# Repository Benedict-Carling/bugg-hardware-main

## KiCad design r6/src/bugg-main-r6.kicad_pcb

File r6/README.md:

# Bugg r6 main board (unofficial, unbuilt)

An experimental revision of the Bugg r5 main board by Benedict Carling (Alauda). **It is not an official Bugg release, and no r6 board has been built or measured.**

It is derived from `r5/src` at commit `e71fd5740865aec2923b8e5c67f93d5d7822d4b3` of [bugg-resources/bugg-hardware-main](https://github.com/bugg-resources/bugg-hardware-main), and is licensed CC BY-NC-SA 4.0 like the original, with credit to Bugg's original hardware authors.

## How it was made

The schematic changes, placement and routing were produced with AI coding agents driving KiCad through scripts, and reviewed by me. The review documents in `review/` are AI-assisted review passes. The design has not been reviewed by an independent electronics engineer.

## What changed

- **Plug-in microphone bias filter.** R104 goes from 0 Ω to 100 Ω with the existing 10 µF C83: calculated 34 dB supply-ripple rejection at 8 kHz, or 26 dB if C83 derates to 4 µF. Q25 (the P3V3 mic-power switch) now takes its supply from before R104, so that output keeps its full voltage.
- **ADC input filter.** C75/C76 go from 180 pF to 4.7 nF C0G: calculated 18 dB more rejection at 1.38 MHz and 0.06 dB loss at 20 kHz. This is an experimental 44.1/48 kHz population; 180 pF remains the alternative.
- **Real-time clock.** The DS3231M becomes an RV-3032-C7: ±2.5 ppm instead of ±5 ppm initial specification over −40 to +85 °C, excluding aging.
- **Wake buffer.** U14 becomes an SN74LVC1G37 in the same footprint, with a Schmitt input suited to the slow RC wake edge. R29/R30/C36 become 100 kΩ / 47 kΩ / 1 µF.
- **3.3 V always-on rail.** A TPS7A02 regulator powers the clock, the wake logic and the voltage monitor, which r5 ran from the approximately 5.4 V system rail against 5.5 V part limits.
- **Supply voltage monitoring.** An ADS1115 measures the input, system, modem and USB rails. It measures voltage only, not current or battery charge.
- **Modem shutdown confirmation.** VGPIO and SAFE_PWR_REMOVE are level-shifted and latched, then read over I²C. This addresses r5 erratum 5.

The full part list is in [review/BOM-CHANGES.md](review/BOM-CHANGES.md): 8 changed, 33 added.

## What did not change

- **Board:** the outline, the six-layer stack and the 1.6 mm thickness.
- **Fixed interfaces:** all 37 keep their position, rotation, side and pad geometry. That covers the CM4, the modem, the USB, J10 and FH12 connectors, both U.FL connectors, the SIM, microSD and coin-cell holders, the mounting holes, bosses, ground contacts, J1–J9 and the fiducials.
- **Copper and test points:** the USB and microphone-input traces are identical to r5, and all 59 r5 test points remain.

## Caveats

- **Nothing is measured.** All figures are calculations or datasheet specifications. There is no claim of lower recorded self-noise, longer battery life or better reliability.
- **KiCad 10 is required.** The files were saved in KiCad 10 format, so the diff against r5 includes format changes.
- **Some sheets were regenerated by script.** The RTC sheet and the two new sheets were written by script rather than edited by hand, so the schematic diffs are larger than the actual changes.
- **Not a drop-in r5 image.** The new RTC and monitoring need Bugg OS integration, and `firmware/` contains support code with 22 unit tests against simulated hardware.
- **Still to validate on a prototype:** ADC settling and distortion, microphone noise, wake timing, modem shutdown timing, power sequencing and enclosure fit.

## Reproducing the checks

Run these from `r6/`:

| Command | What it does |
|---|---|
| `<KiCad 10 python> design/verify_board.py` | Compares the board against `r5/src` and checks schematic/PCB pad nets |
| `python3 design/calculations.py` | Recomputes the filter and clock figures from the netlist |
| `python3 design/bom.py` | Regenerates the BOM delta |
| `cd firmware && python3 -m unittest discover -p 'test_*.py'` | Runs the firmware tests |

The native KiCad results are recorded in `review/final-drc.json` and `review/erc.json`: 0 DRC errors, 0 unconnected items, 0 schematic-parity issues and 0 ERC errors.

Start with [review/REPORT.md](review/REPORT.md). [review/AUDIO-EXPLAINED.md](review/AUDIO-EXPLAINED.md) explains what the filter figures mean for recordings.

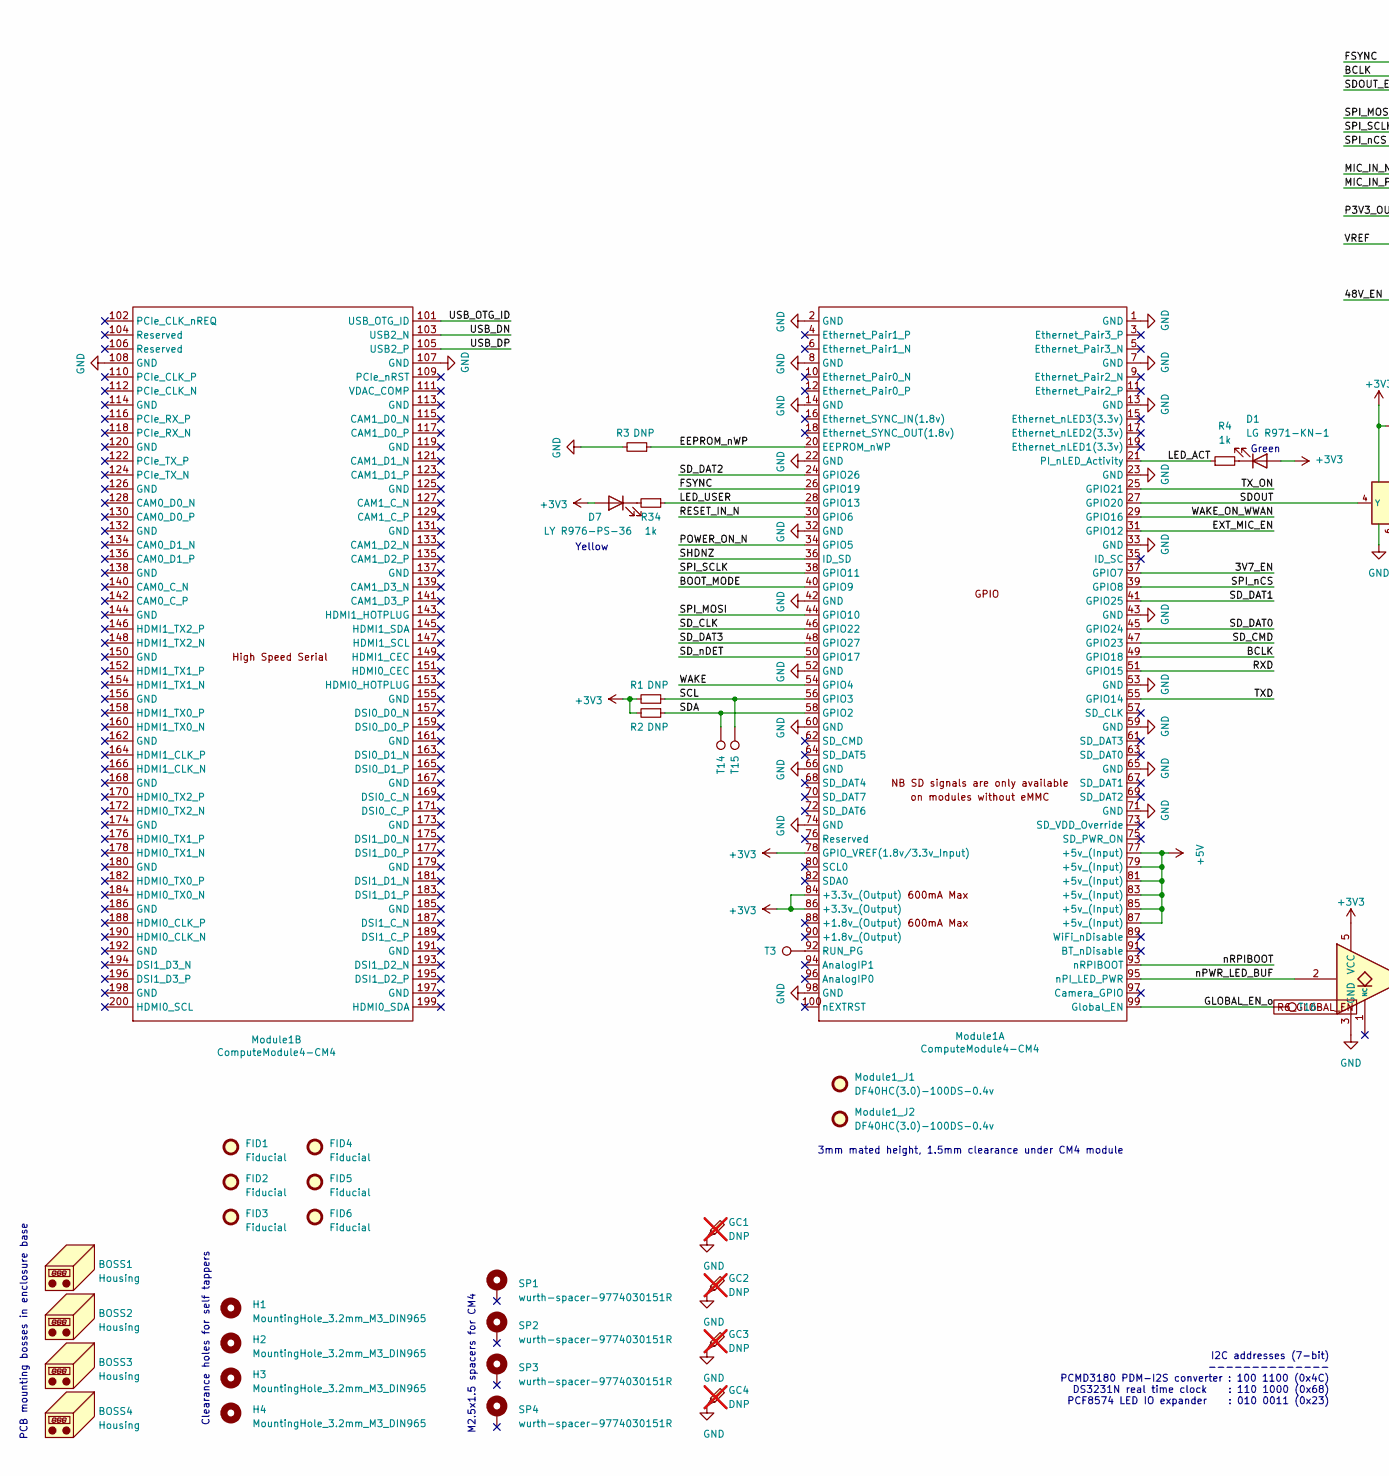
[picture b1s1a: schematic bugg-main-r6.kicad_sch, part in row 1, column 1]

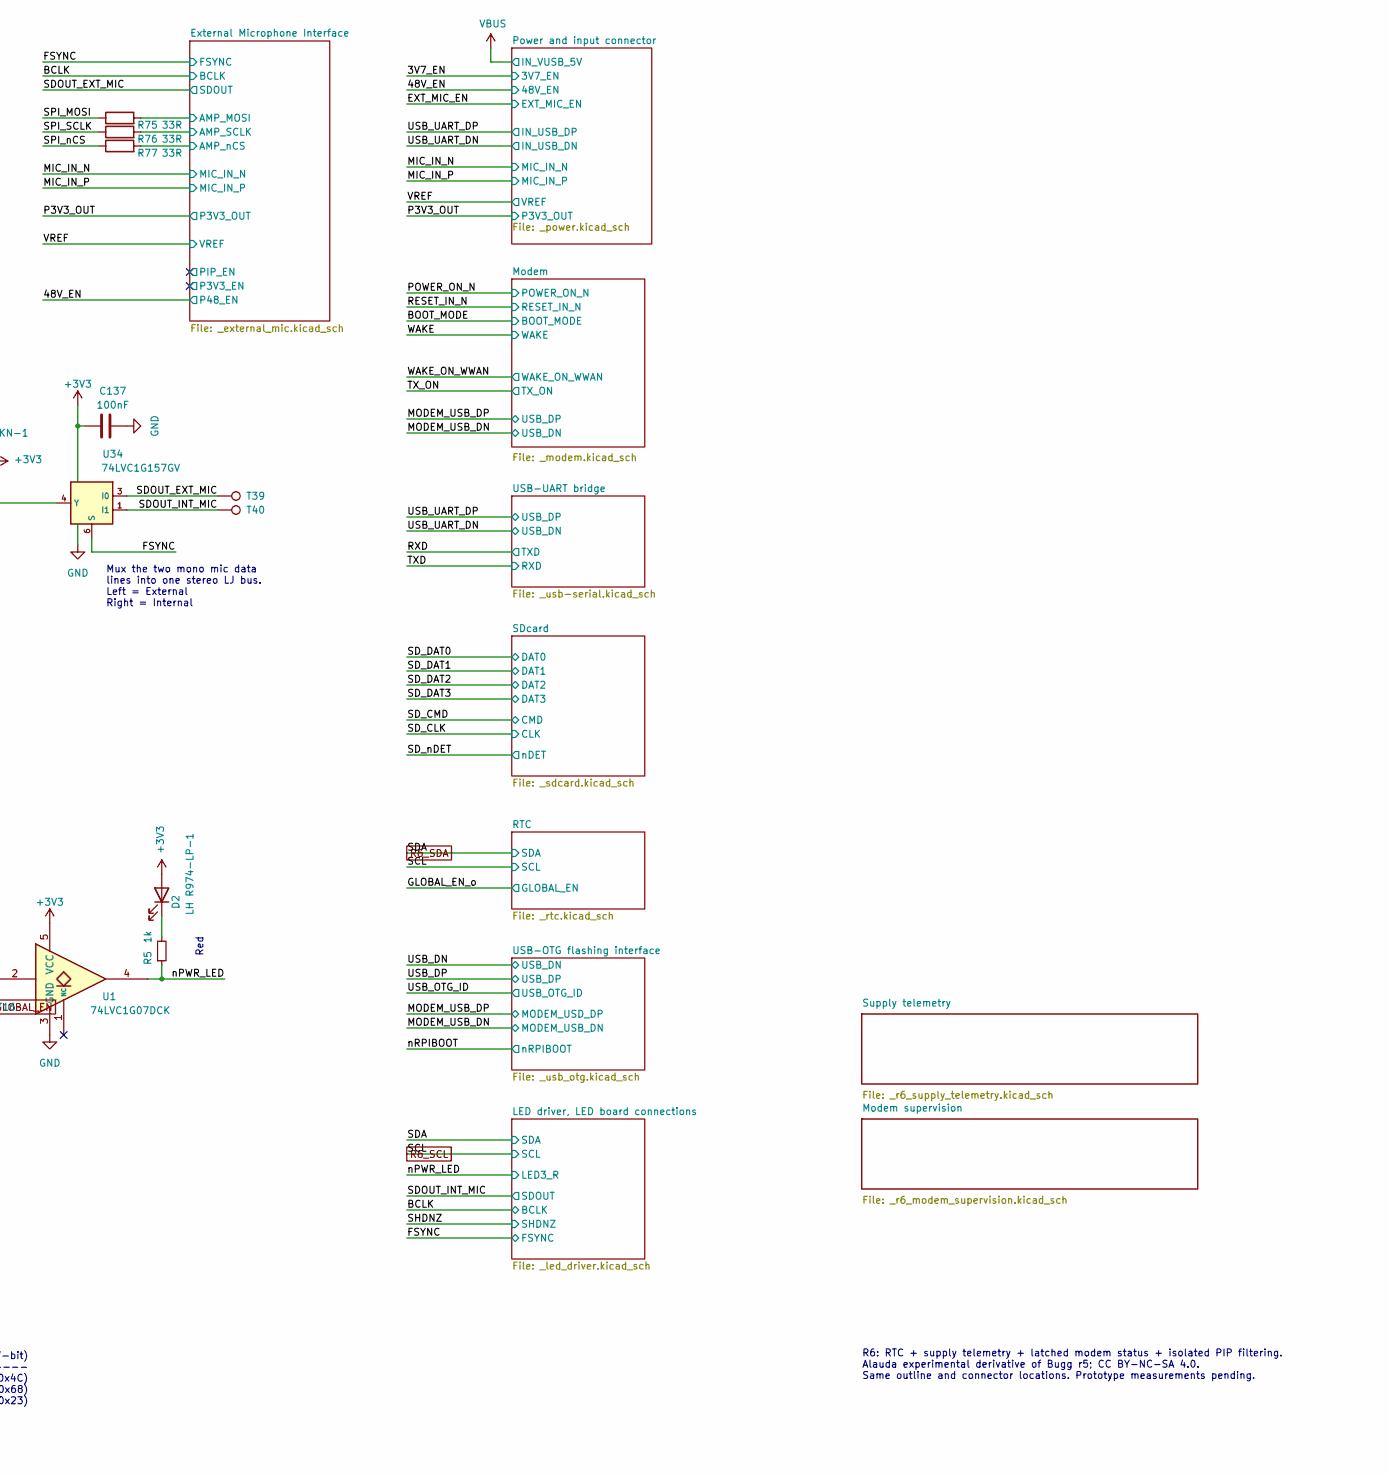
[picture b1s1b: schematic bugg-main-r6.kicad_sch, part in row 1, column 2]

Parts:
BOSS1, BOSS2, BOSS3, BOSS4: Housing; bugg-pcb-boss
C137: 100nF; C_0402_1005Metric; Voltage 50V; MPN GRM155R71H104KE14D; Mouser 81-GRM155R71H104KE4D
D1: LG R971-KN-1; CHIPLED-0805; MPN LGR971-KN-1; Digikey 475-1410-6-ND
D2: LH R974-LP-1; CHIPLED-0805; MPN LHR974-LP-1; Digikey 475-1415-6-ND
D7: LY R976-PS-36; CHIPLED-0805; MPN LYR976-PS-36; Digikey 475-2560-6-ND
FID1, FID2, FID3, FID4, FID5, FID6: Fiducial; Fiducial_1mm_Mask2mm
GC1, GC2, GC3, GC4: DNP; TestPoint_Keystone_5019_Minature; MPN 5019; Mouser 534-5019; not fitted
H1, H2, H3, H4: MountingHole_3.2mm_M3_DIN965
Module1: ComputeModule4-CM4; Raspberry-Pi-4-Compute-Module-no-holes; MPN CM4002016; Farnell 3563481
Module1_J1, Module1_J2: DF40HC(3.0)-100DS-0.4v; MPN DF40HC(3.0)-100DS-0.4v; Digikey H124602DKR-ND
R1, R2, R3: DNP; R_0402_1005Metric
R4, R5, R34: 1k; R_0402_1005Metric
R75, R76, R77: 33R; R_0402_1005Metric
SP1, SP2, SP3, SP4: wurth-spacer-9774030151R; wurth-spacer-WA-SMSI-9774030151R; MPN 9774030151R; Digikey 732-7083-6-ND
T3, T14, T15, T16, T39, T40: TestPoint_Pad_D1.0mm
U1: 74LVC1G07DCK; SOT-353_SC-70-5; MPN SN74LVC1G07DCKT; Digikey 296-26591-6-ND
U34: 74LVC1G157GV; SC-74-6_1.5x2.9mm_P0.95mm; MPN 74LVC1G157GV; Mouser 771-74LVC1G157GVQ100

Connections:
+3V3: C137.2, D1.2 (A), D2.2 (A), D7.2 (A), Module1.78 (GPIO_VREF(1.8v/3.3v_Input)), Module1.84 (+3.3v_(Output)), Module1.86 (+3.3v_(Output)), R1.2, R2.2, U1.5 (VCC), U34.5 (VCC); also elsewhere on the board
+5V: Module1.77 (+5v_(Input)), Module1.79 (+5v_(Input)), Module1.81 (+5v_(Input)), Module1.83 (+5v_(Input)), Module1.85 (+5v_(Input)), Module1.87 (+5v_(Input)); also elsewhere on the board
/3V7_EN: Module1.37 (GPIO7); also elsewhere on the board
/BCLK: Module1.49 (GPIO18); also elsewhere on the board
/BOOT_MODE: Module1.40 (GPIO9); also elsewhere on the board
/EEPROM_nWP: Module1.20 (EEPROM_nWP), R3.1
/EXT_MIC_EN: Module1.31 (GPIO12); also elsewhere on the board
/External Microphone Interface/AMP_MOSI: R75.2; also elsewhere on the board
/External Microphone Interface/AMP_SCLK: R76.2; also elsewhere on the board
/External Microphone Interface/AMP_nCS: R77.2; also elsewhere on the board
/FSYNC: Module1.26 (GPIO19), U34.6 (S); also elsewhere on the board
/LED_ACT: Module1.21 (PI_nLED_Activity), R4.1
/LED_USER: Module1.28 (GPIO13), R34.1
/POWER_ON_N: Module1.34 (GPIO5); also elsewhere on the board
/RESET_IN_N: Module1.30 (GPIO6); also elsewhere on the board
/RXD: Module1.51 (GPIO15); also elsewhere on the board
/SDOUT: Module1.27 (GPIO20), U34.4 (Y)
/SDOUT_EXT_MIC: T39.1, U34.3 (I0); also elsewhere on the board
/SDOUT_INT_MIC: T40.1, U34.1 (I1); also elsewhere on the board
/SD_CLK: Module1.46 (GPIO22); also elsewhere on the board
/SD_CMD: Module1.47 (GPIO23); also elsewhere on the board
/SD_DAT0: Module1.45 (GPIO24); also elsewhere on the board
/SD_DAT1: Module1.41 (GPIO25); also elsewhere on the board
/SD_DAT2: Module1.24 (GPIO26); also elsewhere on the board
/SD_DAT3: Module1.48 (GPIO27); also elsewhere on the board
/SD_nDET: Module1.50 (GPIO17); also elsewhere on the board
/SHDNZ: Module1.36 (ID_SD); also elsewhere on the board
/SPI_MOSI: Module1.44 (GPIO10), R75.1
/SPI_SCLK: Module1.38 (GPIO11), R76.1
/SPI_nCS: Module1.39 (GPIO8), R77.1
/TXD: Module1.55 (GPIO14); also elsewhere on the board
/TX_ON: Module1.25 (GPIO21); also elsewhere on the board
/USB_DN: Module1.103 (USB2_N); also elsewhere on the board
/USB_DP: Module1.105 (USB2_P); also elsewhere on the board
/USB_OTG_ID: Module1.101 (USB_OTG_ID); also elsewhere on the board
/WAKE: Module1.54 (GPIO4); also elsewhere on the board
/WAKE_ON_WWAN: Module1.29 (GPIO16); also elsewhere on the board
/nPWR_LED: R5.1, U1.4; also elsewhere on the board
/nPWR_LED_BUF: Module1.95 (nPI_LED_PWR), U1.2
/nRPIBOOT: Module1.93 (nRPIBOOT); also elsewhere on the board
GND: C137.1, GC1.1, GC2.1, GC3.1, GC4.1, Module1.1 (GND), Module1.2 (GND), Module1.7 (GND), Module1.8 (GND), Module1.13 (GND), Module1.14 (GND), Module1.22 (GND), Module1.23 (GND), Module1.32 (GND), Module1.33 (GND), Module1.42 (GND), Module1.43 (GND), Module1.52 (GND), Module1.53 (GND), Module1.59 (GND), Module1.60 (GND), Module1.65 (GND), Module1.66 (GND), Module1.71 (GND), Module1.74 (GND), Module1.98 (GND), Module1.107 (GND), Module1.108 (GND), R3.2, U1.3 (GND), U34.2 (GND); also elsewhere on the board
unnamed: D1.1 (K), R4.2
unnamed: D2.1 (K), R5.2
unnamed: D7.1 (K), R34.2
unnamed: Module1.92 (RUN_PG), T3.1
R6_GLOBAL_EN: Module1.99 (Global_EN), T16.1; also elsewhere on the board
R6_SCL: Module1.56 (GPIO3), R1.1, T15.1; also elsewhere on the board
R6_SDA: Module1.58 (GPIO2), R2.1, T14.1; also elsewhere on the board

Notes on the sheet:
Yellow
Red
Mux the two mono mic data lines into one stereo LJ bus. Left = External Right = Internal
Green
3mm mated height, 1.5mm clearance under CM4 module
PCB mounting bosses in enclosure base
Clearance holes for self tappers
I2C addresses (7-bit) -------------- PCMD3180 PDM-I2S converter : 100 1100 (0x4C) DS3231N real time clock : 110 1000 (0x68) PCF8574 LED IO expander : 010 0011 (0x23)
M2.5x1.5 spacers for CM4
R6: RTC + supply telemetry + latched modem status + isolated PIP filtering. Alauda experimental derivative of Bugg r5; CC BY-NC-SA 4.0. Same outline and connector locations. Prototype measurements pending.

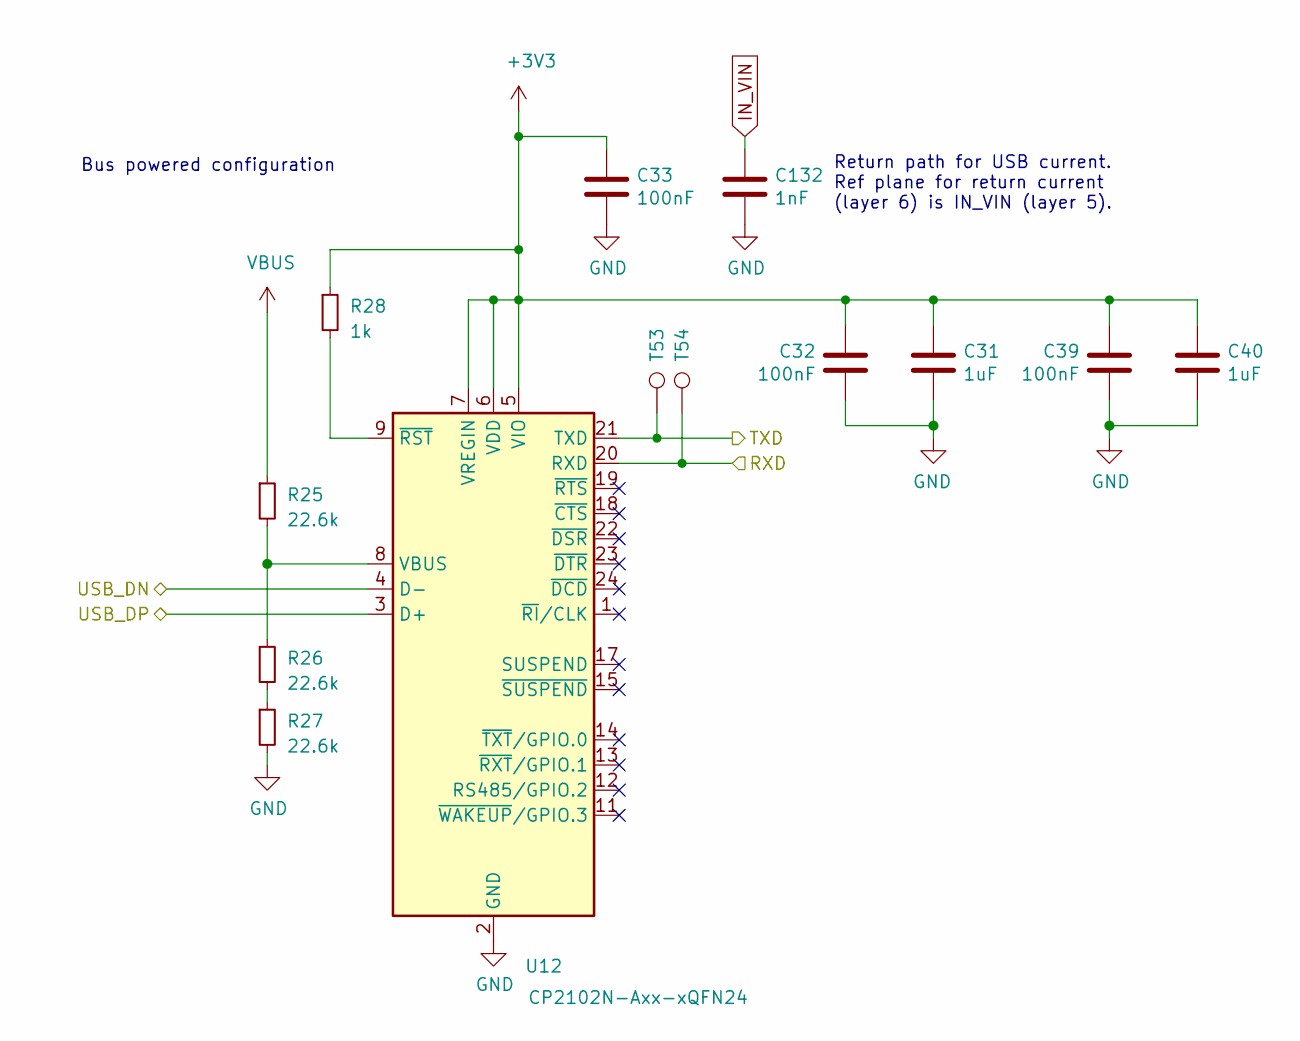
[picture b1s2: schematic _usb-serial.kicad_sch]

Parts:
C31, C40: 1uF; C_0402_1005Metric; Voltage 6.3V; MPN GRM155C81C105KE15D; Mouser 81-GRM155C81C105KE5D
C32, C33, C39: 100nF; C_0402_1005Metric; Voltage 50V; MPN GRM155R71H104KE14D; Mouser 81-GRM155R71H104KE4D
C132: 1nF; C_0402_1005Metric
R25, R26, R27: 22.6k; R_0402_1005Metric
R28: 1k; R_0402_1005Metric
T53, T54: TestPoint_Pad_D1.0mm
U12: CP2102N-Axx-xQFN24; QFN-24-1EP_4x4mm_P0.5mm_EP2.6x2.6mm; MPN CP2102N-A02-GQFN24R; Digikey 336-5888-6-ND

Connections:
+3V3: C31.1, C32.1, C33.1, C39.1, C40.1, R28.1, U12.5 (VIO), U12.6 (VDD), U12.7 (VREGIN); also elsewhere on the board
/RXD: T53.1, U12.21 (TXD); also elsewhere on the board
/TXD: T54.1, U12.20 (RXD); also elsewhere on the board
/USB_UART_DN: U12.4 (D-); also elsewhere on the board
/USB_UART_DP: U12.3 (D+); also elsewhere on the board
GND: C31.2, C32.2, C33.2, C39.2, C40.2, C132.2, R27.2, U12.2 (GND), U12.25 (GND); also elsewhere on the board
IN_VIN: C132.1; also elsewhere on the board
unnamed: R26.2, R27.1
unnamed: R25.2, R26.1, U12.8 (VBUS)
unnamed: R28.2, U12.9 (~RST)
VBUS: R25.1; also elsewhere on the board

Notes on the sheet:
Return path for USB current. Ref plane for return current (layer 6) is IN_VIN (layer 5).
Bus powered configuration

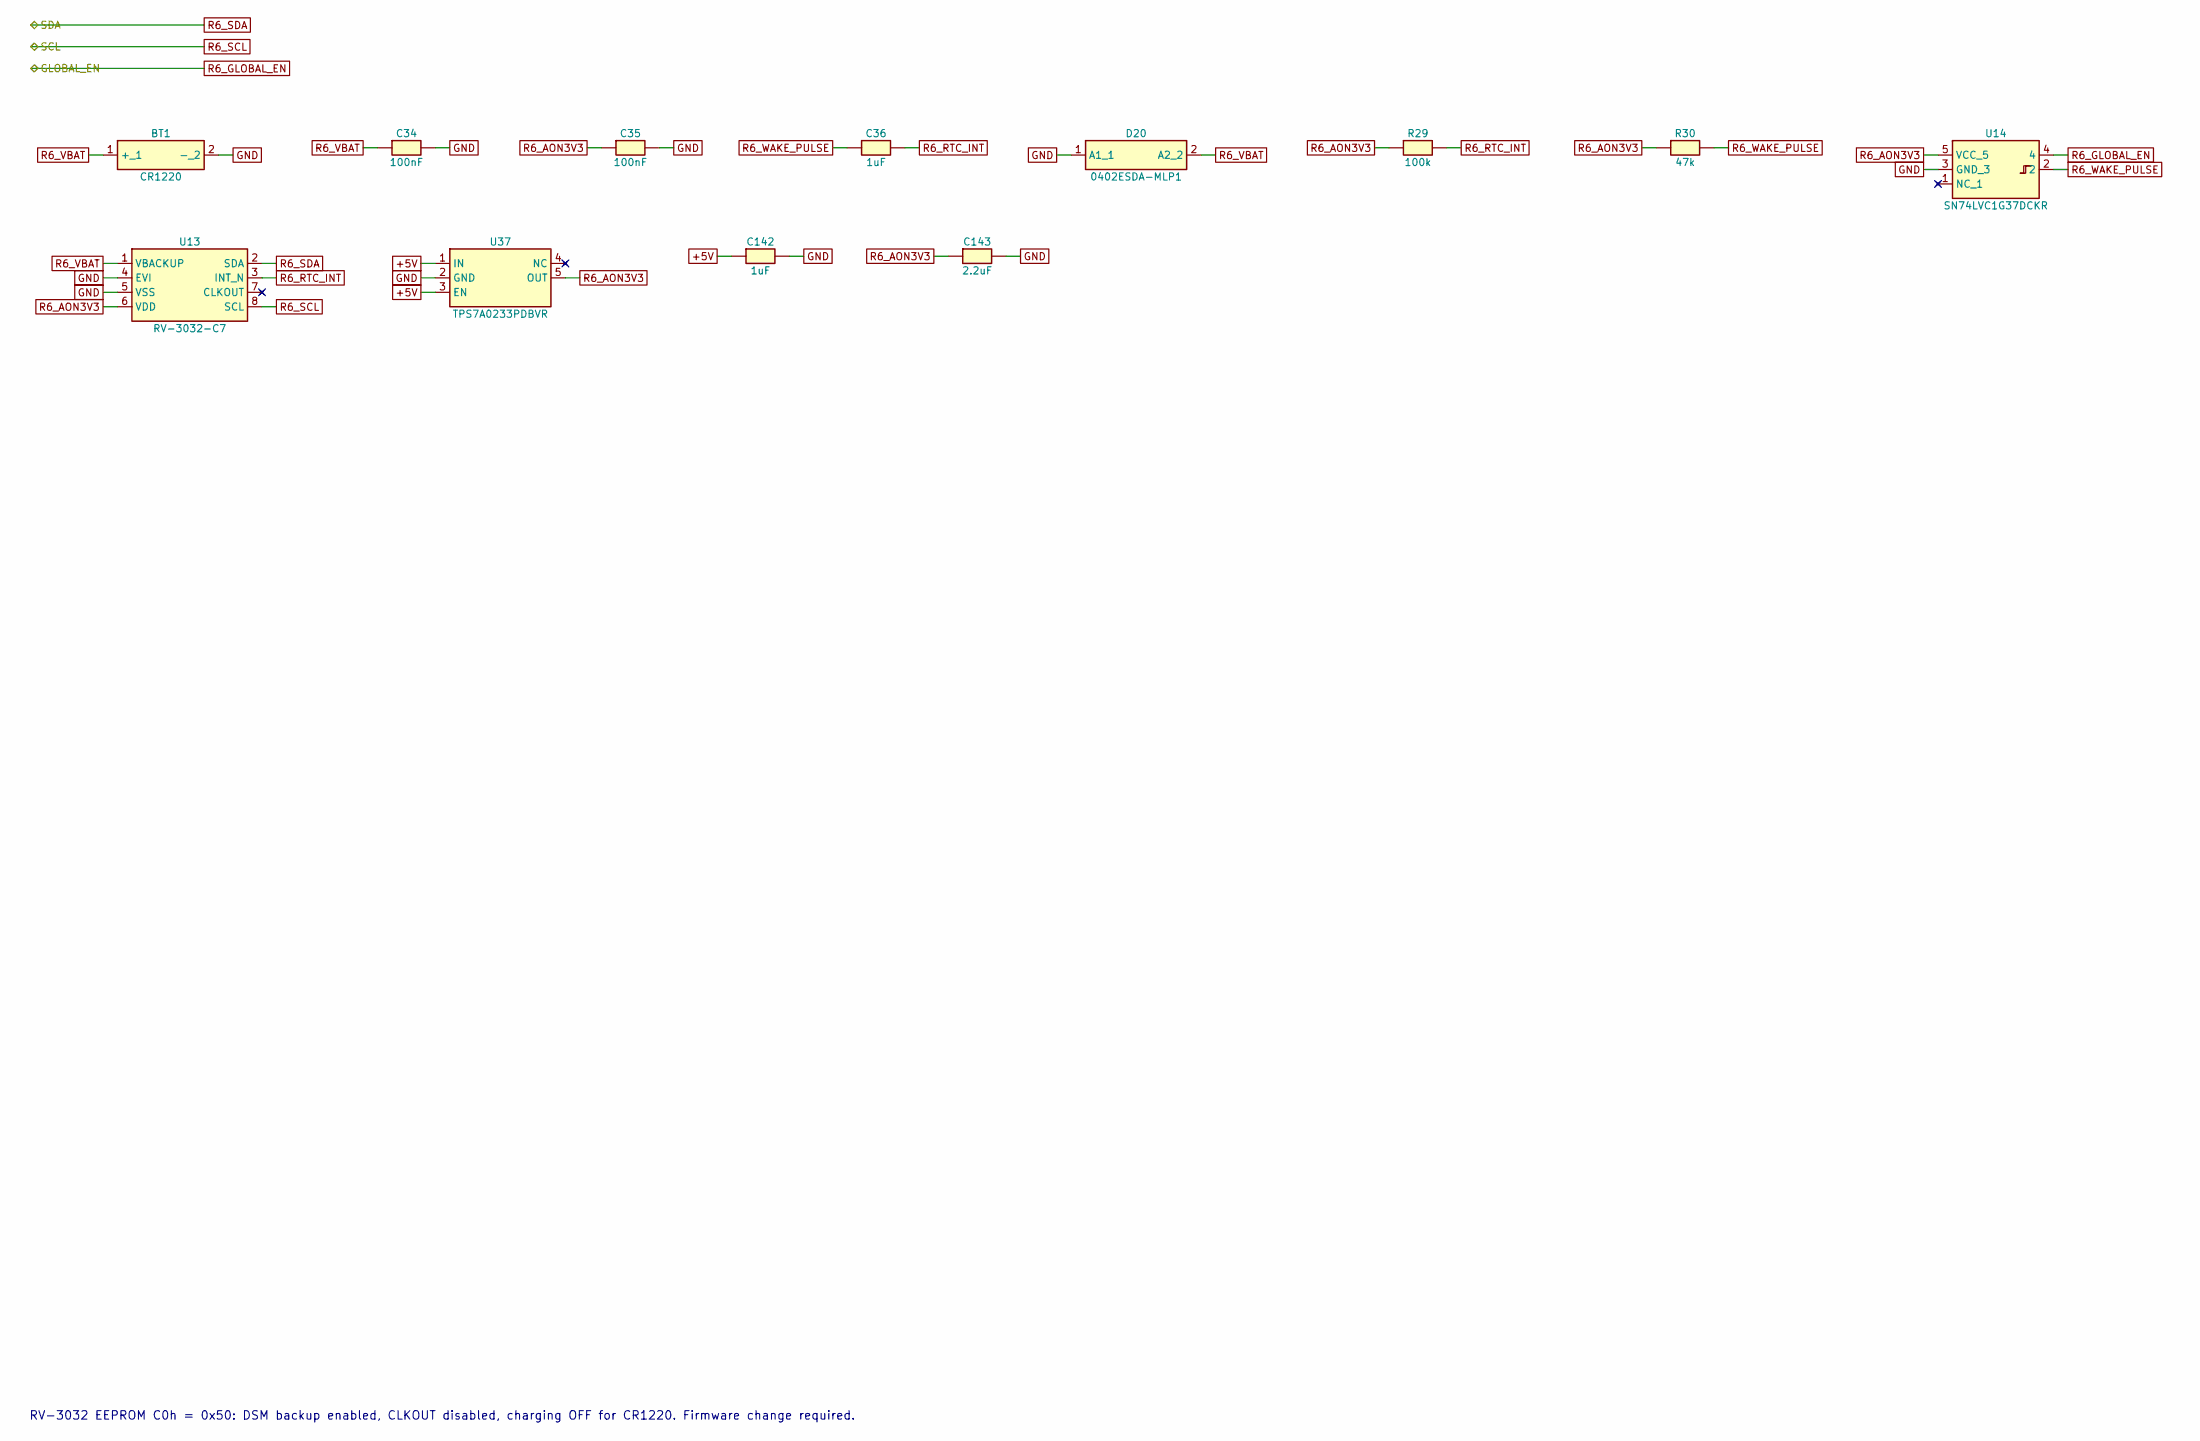
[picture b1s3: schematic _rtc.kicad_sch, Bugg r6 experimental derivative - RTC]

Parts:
BT1: CR1220; Keystone-3000-CR1220-CR1216; MPN 3000TR
C34, C35: 100nF; C_0402_1005Metric; MPN GRM155R71H104KE14D
C36: 1uF; C_0402_1005Metric; MPN GRM155R61C105KA12D
C142: 1uF; C_0603_1608Metric; MPN CL10A105KB8NNNC
C143: 2.2uF; C_0603_1608Metric; MPN CL10A225KP8NNNC
D20: 0402ESDA-MLP1; D_0402_1005Metric; MPN 0402ESDA-MLP1
R29: 100k; R_0402_1005Metric; MPN RC0402FR-07100KL
R30: 47k; R_0402_1005Metric; MPN RC0402FR-0747KL
U13: RV-3032-C7; MicroCrystal_C7_SON-8_1.5x3.2mm_P0.9mm; MPN RV-3032-C7 32.768kHz 2.5ppm TA QC
U14: SN74LVC1G37DCKR; SOT-353_SC-70-5; MPN SN74LVC1G37DCKR
U37: TPS7A0233PDBVR; SOT-23-5; MPN TPS7A0233PDBVR

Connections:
+5V: C142.1, U37.1 (IN), U37.3 (EN); also elsewhere on the board
GND: BT1.2 (-), C34.2, C35.2, C142.2, C143.2, D20.1 (A1), U13.4 (EVI), U13.5 (VSS), U14.3 (GND), U37.2 (GND); also elsewhere on the board
R6_AON3V3: C35.1, C143.1, R29.1, R30.1, U13.6 (VDD), U14.5 (VCC), U37.5 (OUT); also elsewhere on the board
R6_GLOBAL_EN: U14.4; also elsewhere on the board
R6_RTC_INT: C36.2, R29.2, U13.3 (INT_N)
R6_SCL: U13.8 (SCL); also elsewhere on the board
R6_SDA: U13.2 (SDA); also elsewhere on the board
R6_VBAT: BT1.1 (+), C34.1, D20.2 (A2), U13.1 (VBACKUP)
R6_WAKE_PULSE: C36.1, R30.2, U14.2

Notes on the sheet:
RV-3032 EEPROM C0h = 0x50: DSM backup enabled, CLKOUT disabled, charging OFF for CR1220. Firmware change required.
